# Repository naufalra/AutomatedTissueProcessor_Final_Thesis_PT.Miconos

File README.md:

# 2._NaufalFinalThesis_TissueProcessing_PTMiconos

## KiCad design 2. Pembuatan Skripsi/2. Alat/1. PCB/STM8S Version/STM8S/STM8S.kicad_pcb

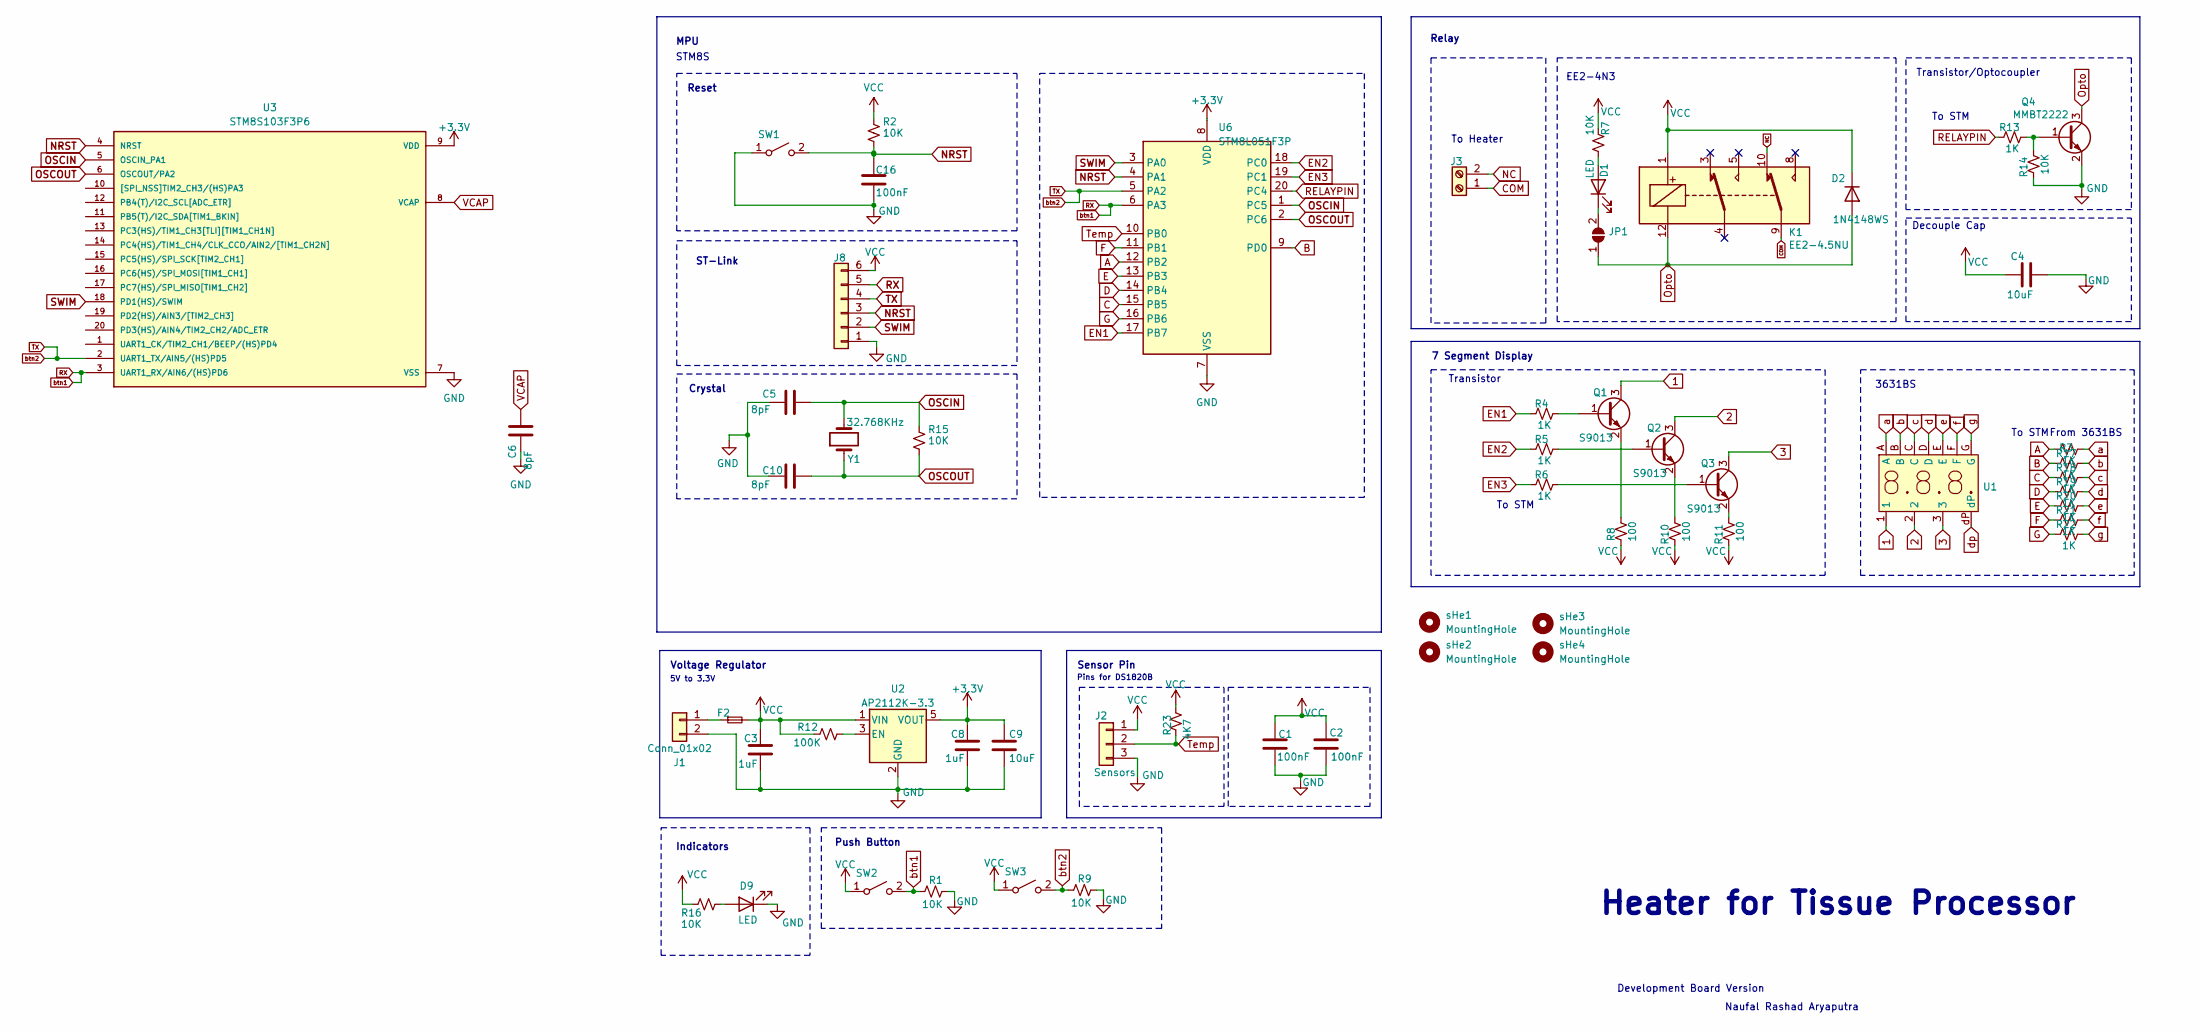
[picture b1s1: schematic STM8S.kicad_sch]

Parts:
C1, C2, C16: 100nF; C_0603_1608Metric_Pad1.08x0.95mm_HandSolder
C3, C8: 1uF; C_0603_1608Metric_Pad1.08x0.95mm_HandSolder
C4, C9: 10uF; C_0603_1608Metric_Pad1.08x0.95mm_HandSolder
C5, C6, C10: 8pF; C_0603_1608Metric_Pad1.08x0.95mm_HandSolder
D1: LED; LED_0603_1608Metric_Pad1.05x0.95mm_HandSolder
D2: 1N4148WS; D_SOD-323
D9: LED; LED_D3.0mm
F2: Fuse_Small; Fuse_1812_4532Metric_Pad1.30x3.40mm_HandSolder
J1: Conn_01x02; JST_XH_B2B-XH-A_1x02_P2.50mm_Vertical
J2: Sensors; JST_XH_B3B-XH-A_1x03_P2.50mm_Vertical
J3: Screw_Terminal_01x02; TerminalBlock_Phoenix_MKDS-1,5-2-5.08_1x02_P5.08mm_Horizont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
J8: Conn_01x06; PinHeader_1x06_P2.54mm_Vertical
JP1: SolderJumper_2_Open; SolderJumper-2_P1.3mm_Open_TrianglePad1.0x1.5mm
K1: EE2-4.5NU; Relay_DPDT_Kemet_EE2_NU
Q1, Q2, Q3: S9013; SOT-23
Q4: MMBT2222; SOT-23
R1, R2, R7, R9, R14, R15, R16: 10K; R_0603_1608Metric_Pad0.98x0.95mm_HandSolder
R3, R4, R5, R6, R13, R17, R18, R19, R20, R21, R22: 1K; R_0603_1608Metric_Pad0.98x0.95mm_HandSolder
R8, R10, R11: 100; R_0603_1608Metric_Pad0.98x0.95mm_HandSolder
R12: 100K; R_0603_1608Metric_Pad0.98x0.95mm_HandSolder
R23: 4K7; R_0603_1608Metric_Pad0.98x0.95mm_HandSolder
SW1: SW_SPST; SW_PUSH_6mm_H5mm
SW2, SW3: SW_SPST; SW_PUSH_6mm_H13mm
U1: 3631BS 7Segment 3Digit
U2: AP2112K-3.3; SOT-23-5
U3: STM8S103F3P6; SOP65P640X120-20N
U6: STM8L051F3P; TSSOP-20_4.4x6.5mm_P0.65mm
Y1: 32.768KHz; Crystal_SMD_SeikoEpson_MC306-4Pin_8.0x3.2mm
sHe1, sHe2, sHe3, sHe4: MountingHole; MountingHole_3mm_Pad_Via

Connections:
1: Q1.3 (C), U1.1
2: Q2.3 (C), U1.2
3: Q3.3 (C), U1.3
+3.3V: C8.1, C9.1, U2.5 (VOUT), U3.9 (VDD), U6.8 (VDD)
A: R3.2, U6.12 (PB2)
B: R17.2, U6.9 (PD0)
C: R18.2, U6.15 (PB5)
COM: J3.1, K1.9
D: R19.2, U6.14 (PB4)
E: R20.2, U6.13 (PB3)
EN1: R4.2, U6.17 (PB7)
EN2: R5.2, U6.18 (PC0)
EN3: R6.2, U6.19 (PC1)
F: R21.2, U6.11 (PB1)
G: R22.2, U6.16 (PB6)
GND: C1.2, C2.2, C3.2, C4.2, C5.2, C6.2, C8.2, C9.2, C10.2, C16.2, D9.1 (K), J1.2, J2.3, J8.1, Q4.2 (E), R1.1, R9.1, R14.2, SW1.1 (A), U2.2 (GND), U3.7 (VSS), U6.7 (VSS)
NC: J3.2, K1.10
NRST: C16.1, J8.3, R2.1, SW1.2 (B), U3.4 (NRST), U6.4 (PA1)
unnamed: D1.2 (A), R7.2
unnamed: D1.1 (K), JP1.2 (B)
unnamed: D9.2 (A), R16.2
unnamed: F2.1, J1.1
unnamed: Q1.1 (B), R4.1
unnamed: Q1.2 (E), R8.1
unnamed: Q2.1 (B), R5.1
unnamed: Q2.2 (E), R10.1
unnamed: Q3.1 (B), R6.1
unnamed: Q3.2 (E), R11.1
unnamed: Q4.1 (B), R13.1, R14.1
unnamed: R12.2, U2.3 (EN)
OSCIN: C5.1, R15.2, U3.5 (OSCIN_PA1), U6.1 (PC5), Y1.2
OSCOUT: C10.1, R15.1, U3.6 (OSCOUT/PA2), U6.2 (PC6), Y1.1
Opto: D2.2 (A), JP1.1 (A), K1.12, Q4.3 (C)
RELAYPIN: R13.2, U6.20 (PC4)
RX: J8.5, R1.2, SW2.2 (B), U3.3 (UART1_RX/AIN6/(HS)PD6), U6.6 (PA3)
SWIM: J8.2, U3.18 (PD1(HS)/SWIM), U6.3 (PA0)
TX: J8.4, R9.2, SW3.2 (B), U3.2 (UART1_TX/AIN5/(HS)PD5), U6.5 (PA2)
Temp: J2.2, R23.1, U6.10 (PB0)
VCAP: C6.1, U3.8 (VCAP)
VCC: C1.1, C2.1, C3.1, C4.1, D2.1 (K), F2.2, J2.1, J8.6, K1.1, R2.2, R7.1, R8.2, R10.2, R11.2, R12.1, R16.1, R23.2, SW2.1 (A), SW3.1 (A), U2.1 (VIN)
a: R3.1, U1.A
b: R17.1, U1.B
c: R18.1, U1.C
d: R19.1, U1.D
dp: U1.dP
e: R20.1, U1.E
f: R21.1, U1.F
g: R22.1, U1.G

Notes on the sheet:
5V to 3.3V
Reset
To STM
Indicators
To Heater
Crystal
Sensor Pin
Development Board Version
7 Segment Display
ST-Link
Naufal Rashad Aryaputra
EE2-4N3
Push Button
Heater for Tissue Processor
Decouple Cap
Relay
Voltage Regulator
Transistor
STM8S
MPU
From 3631BS
Transistor/Optocoupler
3631BS
Pins for DS1820B

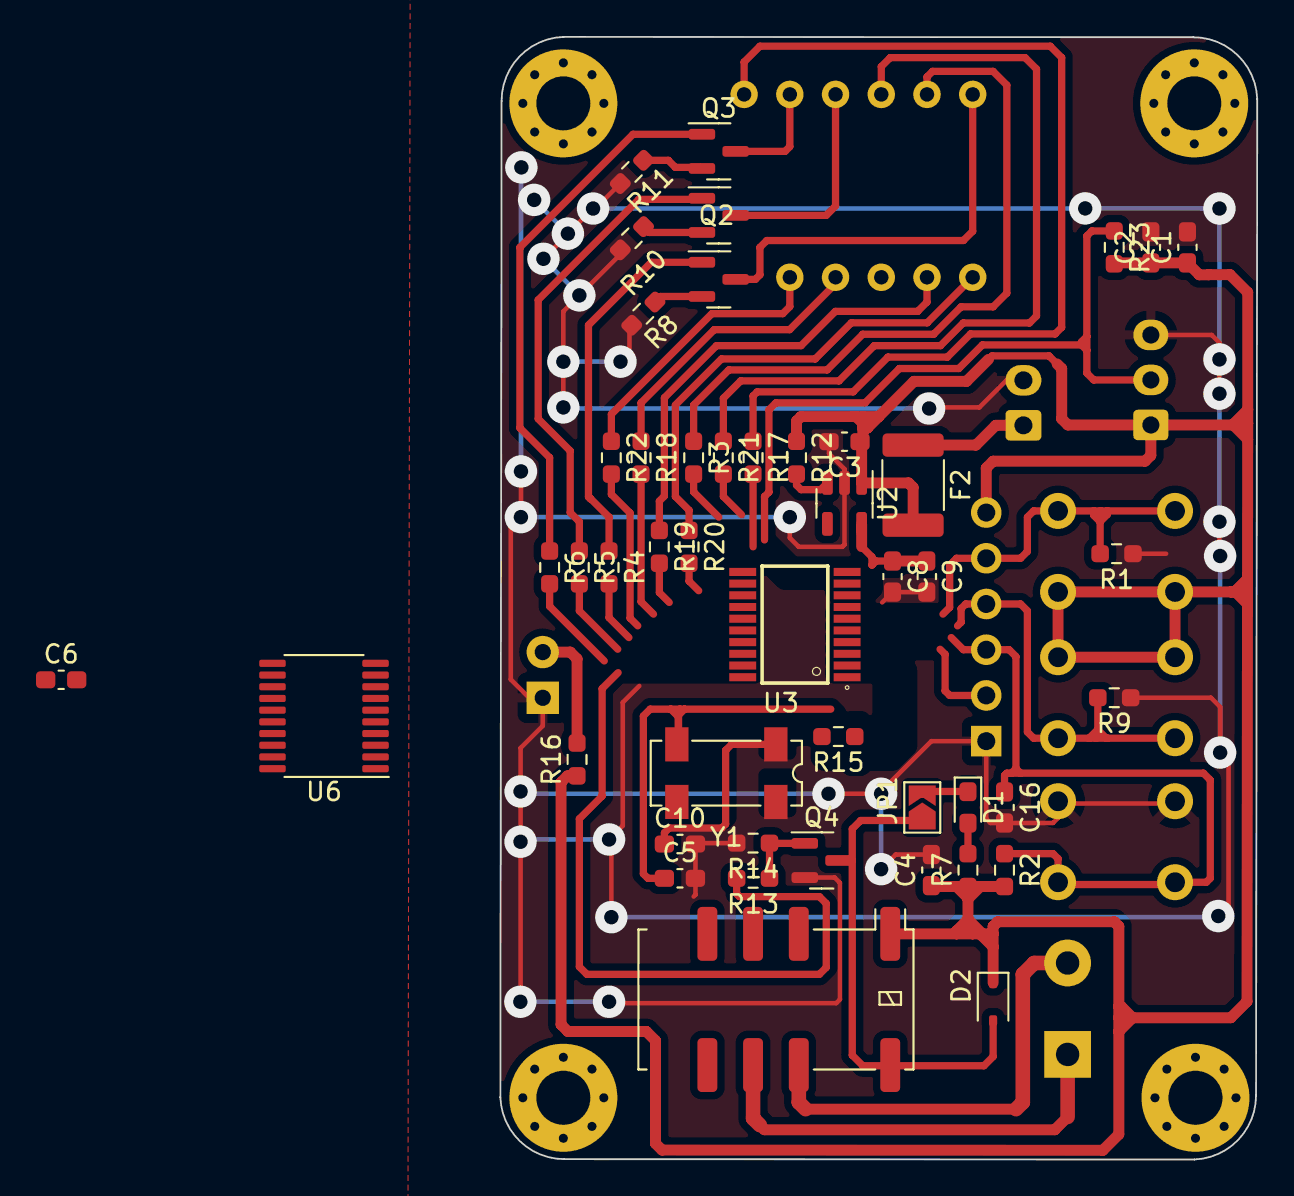
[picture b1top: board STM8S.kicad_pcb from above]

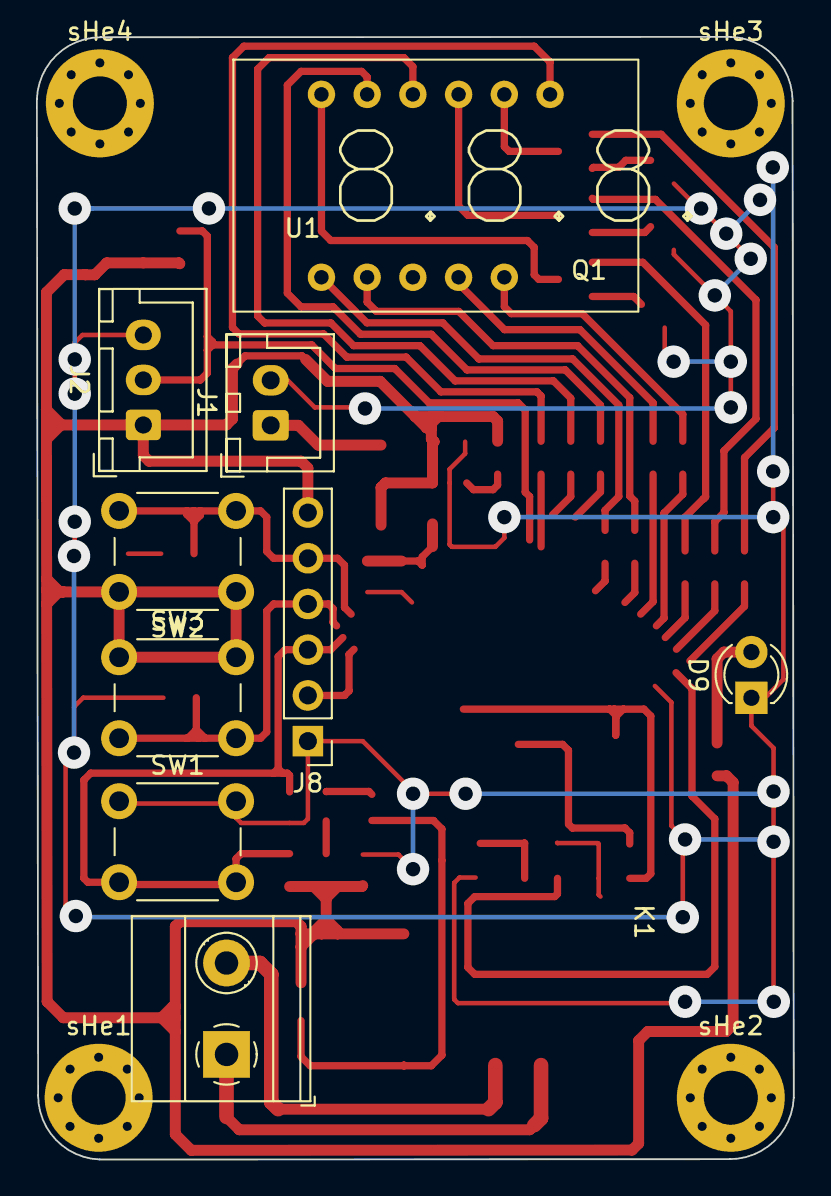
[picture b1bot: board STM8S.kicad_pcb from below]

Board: 2 copper layers, 42.0 x 62.4 mm, 59 parts (13 on the bottom side), 47 nets.

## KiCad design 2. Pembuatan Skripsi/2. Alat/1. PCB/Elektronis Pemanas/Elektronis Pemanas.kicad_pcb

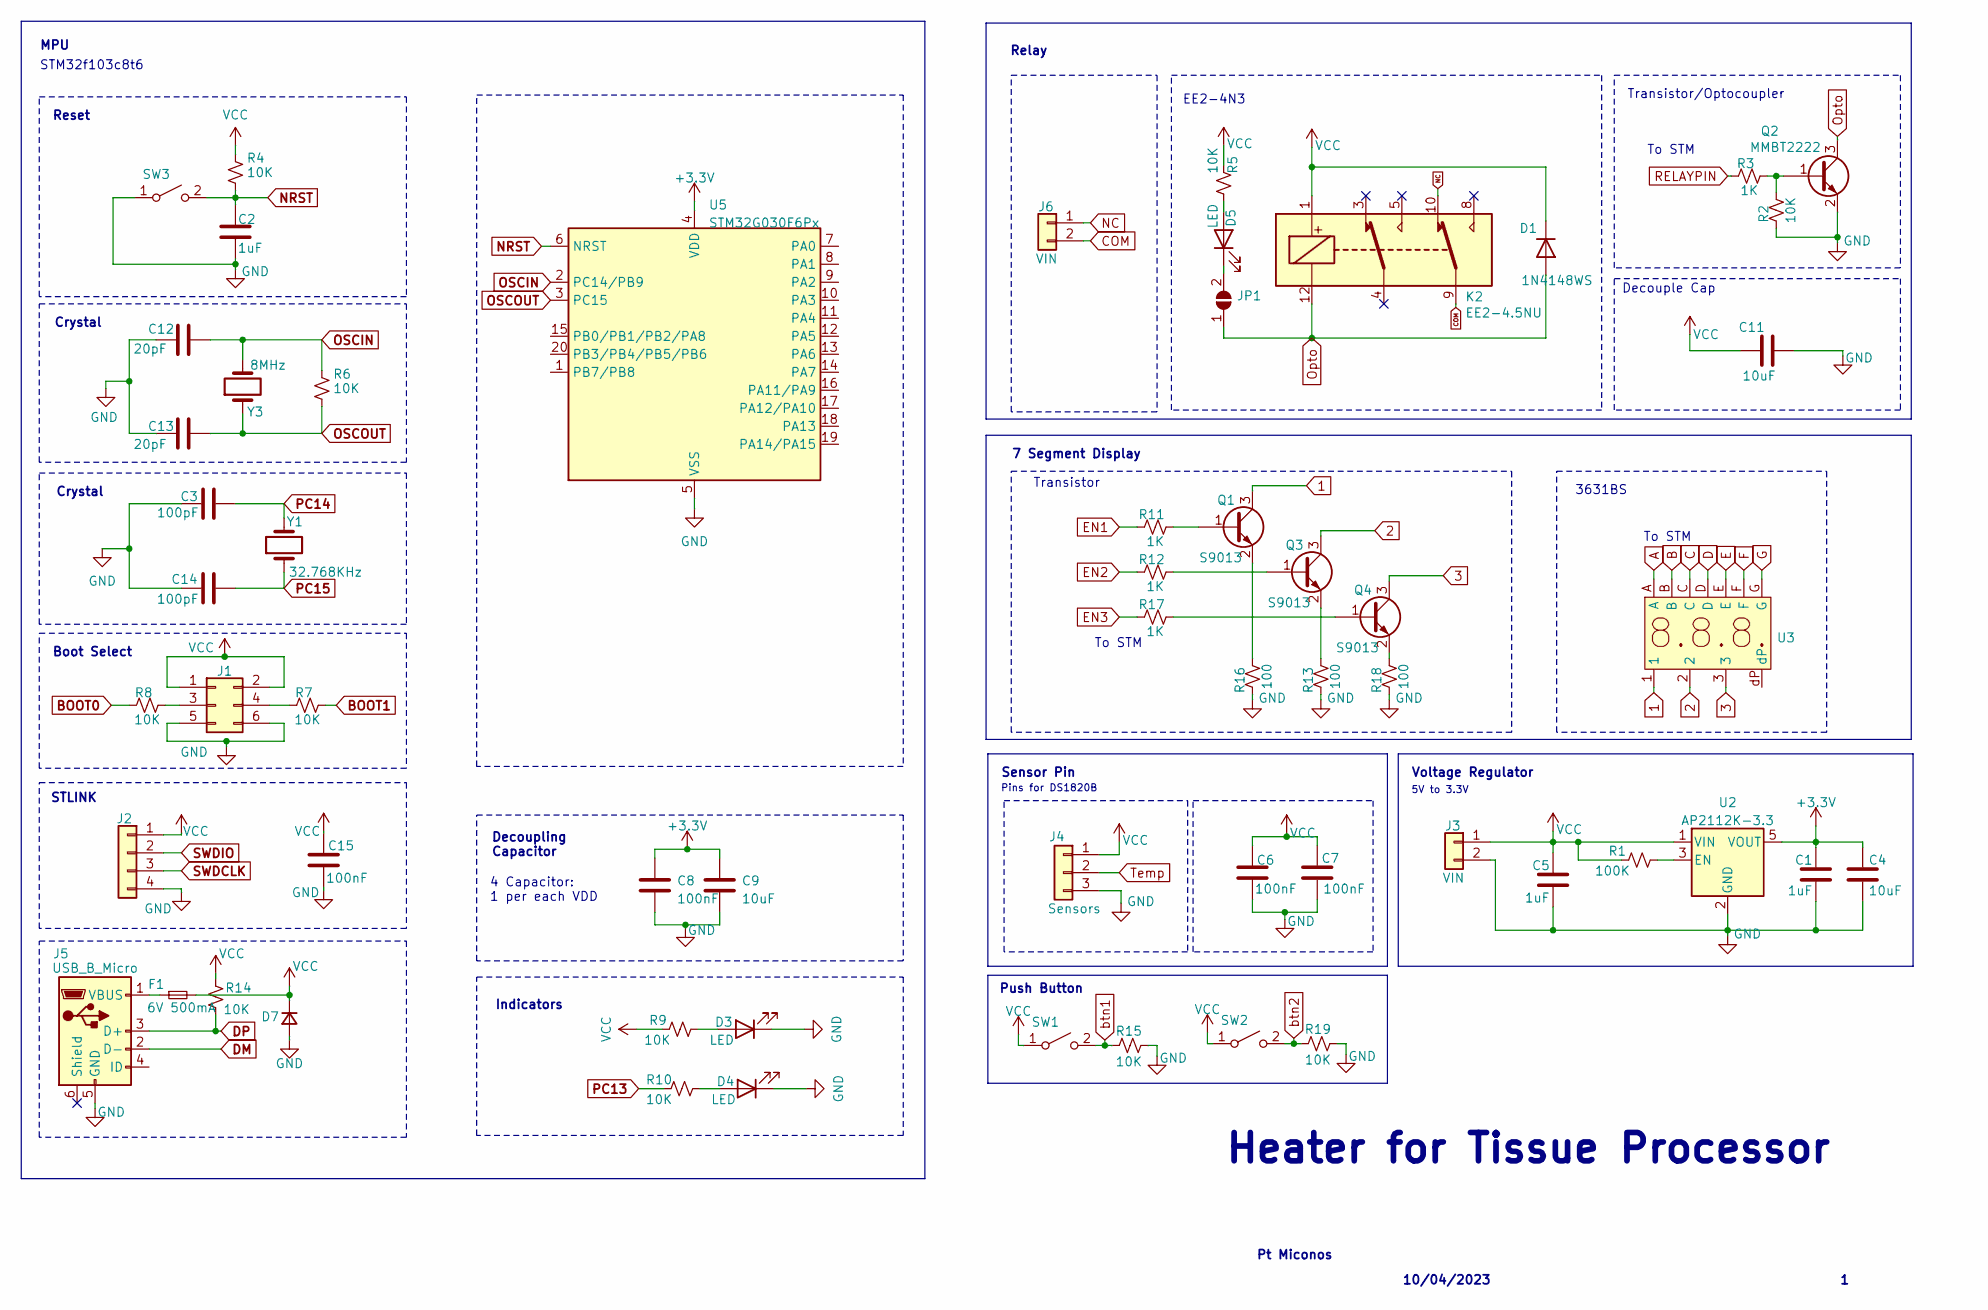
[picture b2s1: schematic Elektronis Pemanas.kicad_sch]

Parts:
C1, C2, C5: 1uF; C_0603_1608Metric_Pad1.08x0.95mm_HandSolder
C3, C14: 100pF; C_0603_1608Metric_Pad1.08x0.95mm_HandSolder
C4, C9, C11: 10uF; C_0603_1608Metric_Pad1.08x0.95mm_HandSolder
C6, C7, C8, C15: 100nF; C_0603_1608Metric_Pad1.08x0.95mm_HandSolder
C12, C13: 20pF; C_0603_1608Metric_Pad1.08x0.95mm_HandSolder
D1: 1N4148WS; D_SOD-323
D3: LED; LED_D3.0mm
D4, D5: LED; LED_0805_2012Metric_Pad1.15x1.40mm_HandSolder
D7: D_Small; D_SMA-SMB_Universal_Handsoldering
F1: 6V 500mA; Fuse_1812_4532Metric_Pad1.30x3.40mm_HandSolder
J1: Conn_02x03_Odd_Even; IDC-Header_2x03_P2.54mm_Vertical
J2: Conn_01x04; JST_XH_B4B-XH-A_1x04_P2.50mm_Vertical
J3, J6: VIN; Banana_Jack_2Pin
J4: Sensors; JST_XH_B3B-XH-A_1x03_P2.50mm_Vertical
J5: USB_B_Micro; USB_Mini-B_Lumberg_2486_01_Horizontal
JP1: SolderJumper_2_Open; SolderJumper-2_P1.3mm_Open_TrianglePad1.0x1.5mm
K2: EE2-4.5NU; Relay_DPDT_Kemet_EE2_NU
Q1, Q3, Q4: S9013; SOT-23
Q2: MMBT2222; SOT-23
R1: 100K; R_0603_1608Metric_Pad0.98x0.95mm_HandSolder
R2, R4, R5, R6, R7, R8, R9, R10, R14, R15, R19: 10K; R_0603_1608Metric_Pad0.98x0.95mm_HandSolder
R3, R11, R12, R17: 1K; R_0603_1608Metric_Pad0.98x0.95mm_HandSolder
R13, R16, R18: 100; R_0603_1608Metric_Pad0.98x0.95mm_HandSolder
SW1, SW2: SW_SPST; SW_PUSH_6mm_H13mm
SW3: SW_SPST; SW_PUSH_6mm_H5mm
U2: AP2112K-3.3; SOT-23-5
U3: 3631BS 7Segment 3Digit
U5: STM32G030F6Px; TSSOP-20_4.4x6.5mm_P0.65mm
Y1: 32.768KHz; Crystal_SMD_SeikoEpson_MC306-4Pin_8.0x3.2mm_HandSoldering
Y3: 8MHz; Crystal_SMD_HC49-SD

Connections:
1: Q1.3 (C), U3.1
2: Q3.3 (C), U3.2
3: Q4.3 (C), U3.3
+3.3V: C1.1, C4.1, C8.1, C9.1, U2.5 (VOUT), U5.4 (VDD)
A: U3.A
B: U3.B
BOOT0: R8.2
BOOT1: R7.1
C: U3.C
COM: J6.2, K2.9
D: U3.D
DM: J5.2 (D-)
DP: J5.3 (D+), R14.1
E: U3.E
EN1: R11.2
EN2: R12.2
EN3: R17.2
F: U3.F
G: U3.G
GND: C1.2, C2.2, C3.2, C4.2, C5.2, C6.2, C7.2, C8.2, C9.2, C11.2, C12.2, C13.2, C14.2, C15.2, D3.1 (K), D4.1 (K), D7.2 (A), J1.5, J1.6, J2.4, J3.2, J4.3, J5.5 (GND), Q2.2 (E), R2.2, R13.2, R15.1, R16.2, R18.2, R19.1, SW3.1 (A), U2.2 (GND), U5.5 (VSS)
NC: J6.1, K2.10
NRST: C2.1, R4.1, SW3.2 (B), U5.6 (NRST)
unnamed: D3.2 (A), R9.2
unnamed: D4.2 (A), R10.2
unnamed: D5.2 (A), R5.2
unnamed: D5.1 (K), JP1.2 (B)
unnamed: J1.3, R8.1
unnamed: J1.4, R7.2
unnamed: F1.1, J5.1 (VBUS)
unnamed: Q1.1 (B), R11.1
unnamed: Q1.2 (E), R16.1
unnamed: Q2.1 (B), R2.1, R3.1
unnamed: Q3.1 (B), R12.1
unnamed: Q3.2 (E), R13.1
unnamed: Q4.1 (B), R17.1
unnamed: Q4.2 (E), R18.1
unnamed: R1.2, U2.3 (EN)
OSCIN: C12.1, R6.2, U5.2 (PC14/PB9), Y3.2
OSCOUT: C13.1, R6.1, U5.3 (PC15), Y3.1
Opto: D1.2 (A), JP1.1 (A), K2.12, Q2.3 (C)
PC13: R10.1
PC14: C3.1, Y1.2
PC15: C14.1, Y1.1
RELAYPIN: R3.2
SWDCLK: J2.3
SWDIO: J2.2
Temp: J4.2
VCC: C5.1, C6.1, C7.1, C11.1, C15.1, D1.1 (K), D7.1 (K), F1.2, J1.1, J1.2, J2.1, J3.1, J4.1, K2.1, R1.1, R4.2, R5.1, R9.1, R14.2, SW1.1 (A), SW2.1 (A), U2.1 (VIN)
btn1: R15.2, SW1.2 (B)
btn2: R19.2, SW2.2 (B)

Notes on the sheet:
5V to 3.3V
EE2-4N3
Transistor
Crystal
To STM
Decouple Cap
7 Segment Display
Heater for Tissue Processor
Relay
Sensor Pin
Boot Select
STLINK
Voltage Regulator
Transistor/Optocoupler
3631BS
Reset
10/04/2023
Push Button
MPU
STM32f103c8t6
Pins for DS1820B
4 Capacitor: 1 per each VDD
Pt Miconos
Indicators
Decoupling Capacitor

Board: 2 copper layers, 59 parts (0 on the bottom side), 32 nets, no tracks yet.

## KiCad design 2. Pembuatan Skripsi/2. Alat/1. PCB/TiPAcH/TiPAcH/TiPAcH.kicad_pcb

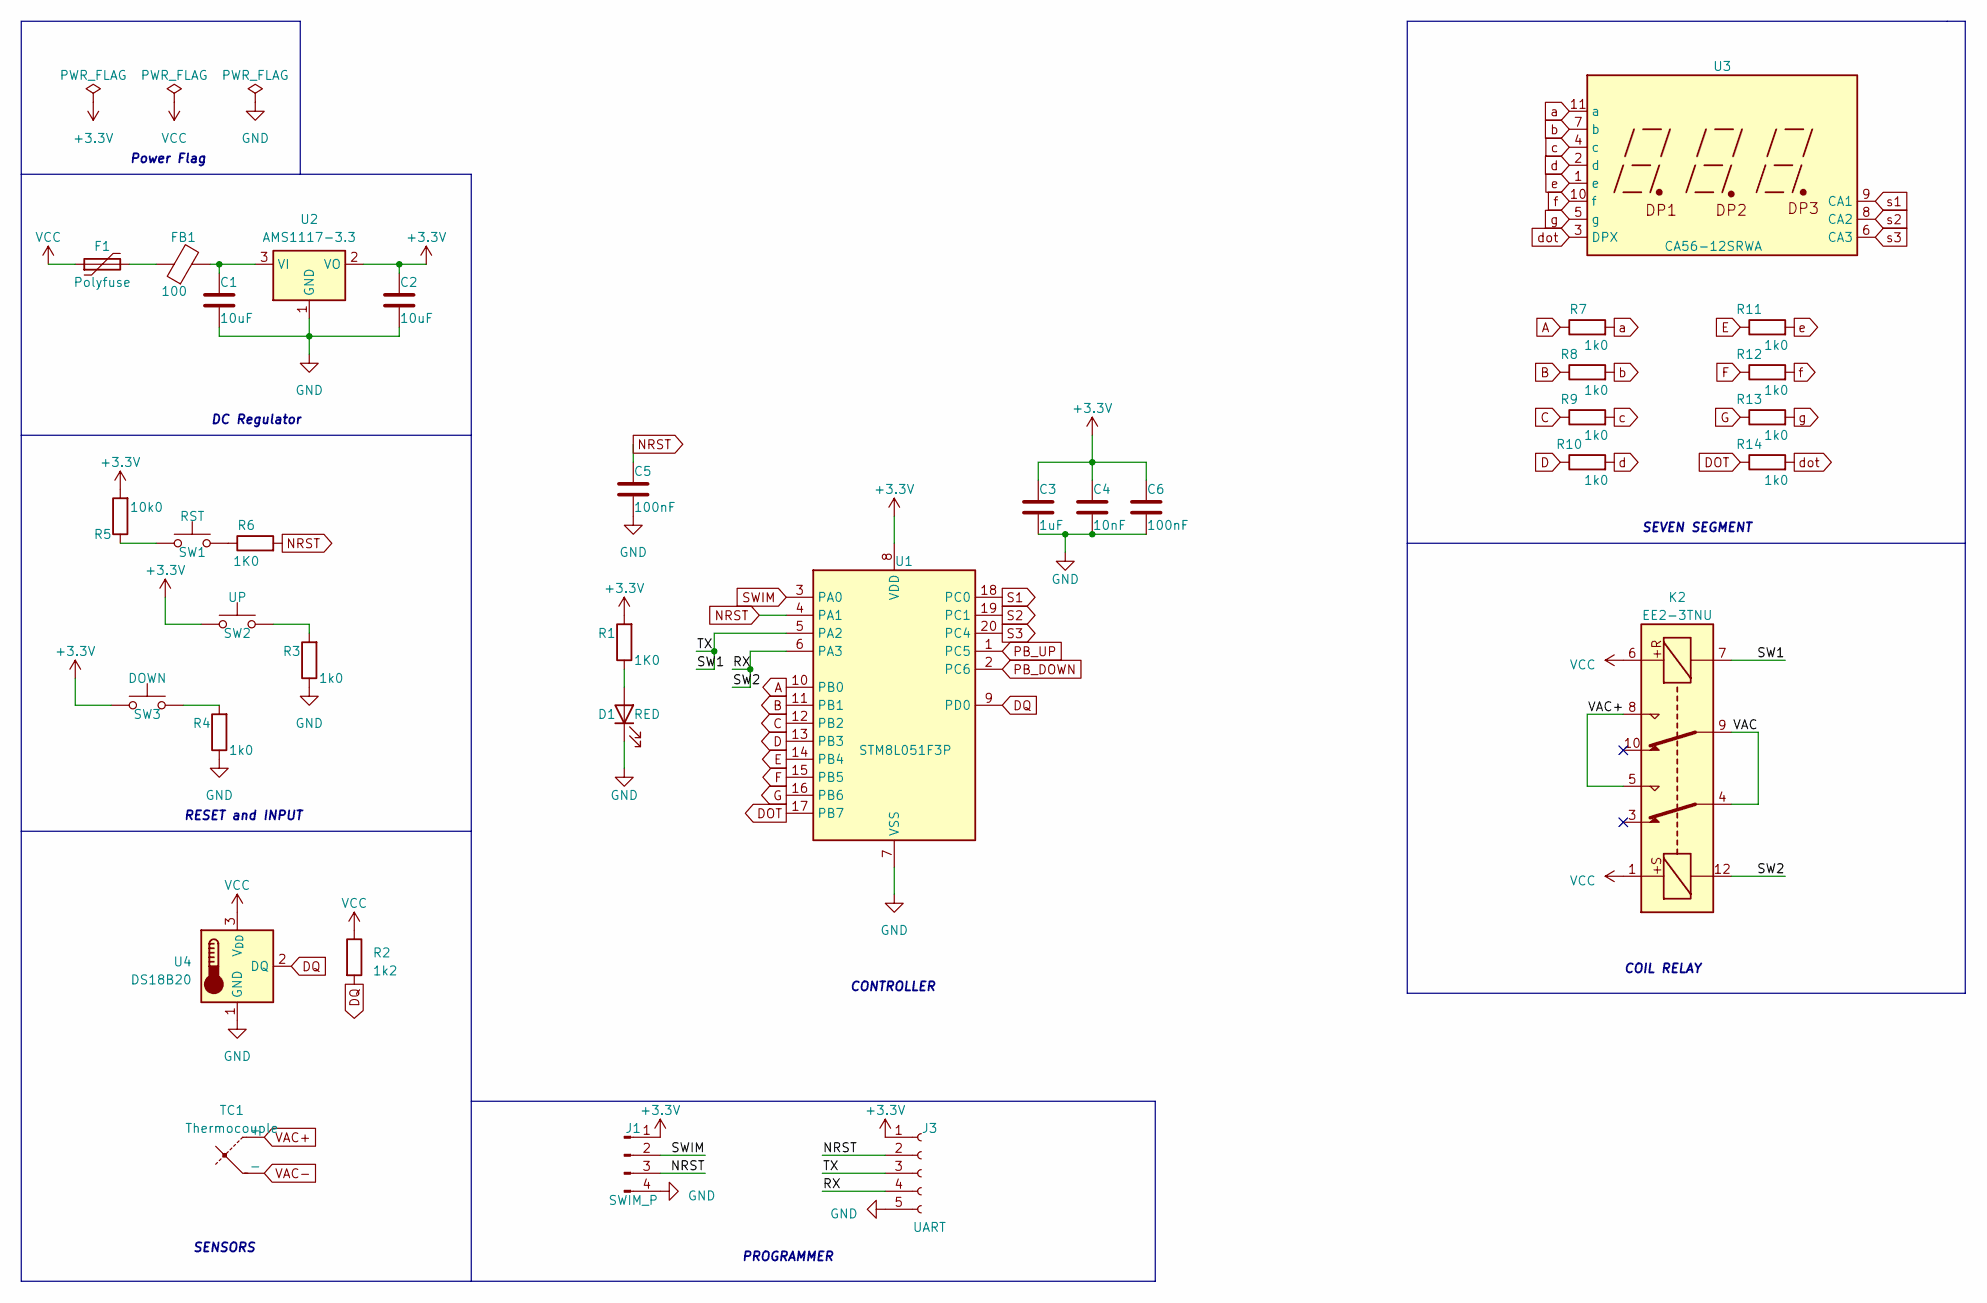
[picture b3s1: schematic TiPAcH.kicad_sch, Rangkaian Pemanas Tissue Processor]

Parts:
C1, C2: 10uF; C_1206_3216Metric
C3: 1uF; C_1206_3216Metric
C4: 10nF; C_1206_3216Metric
C5, C6: 100nF; C_1206_3216Metric
D1: RED; LED_1206_3216Metric
F1: Polyfuse; Fuse_2512_6332Metric
FB1: 100; R_1206_3216Metric
J1: SWIM_P; PinSocket_1x04_P2.54mm_Horizontal
J3: UART; PinSocket_1x05_P2.54mm_Horizontal
K2: EE2-3TNU; Relay_DPDT_Kemet_EE2_NU_DoubleCoil
R1, R6: 1K0; R_1206_3216Metric
R2: 1k2; R_1206_3216Metric
R3, R4, R7, R8, R9, R10, R11, R12, R13, R14: 1k0; R_1206_3216Metric
R5: 10k0; R_1206_3216Metric
SW1: RST; SW_SPST_Omron_B3FS-100xP
SW2: UP; SW_SPST_Omron_B3FS-100xP
SW3: DOWN; SW_SPST_Omron_B3FS-100xP
TC1: Thermocouple; PinSocket_1x02_P2.54mm_Horizontal
U1: STM8L051F3P; TSSOP-20_4.4x6.5mm_P0.65mm
U2: AMS1117-3.3; SOT-223-3_TabPin2
U3: CA56-12SRWA
U4: DS18B20; TO-92_Inline

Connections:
+3.3V: C2.1, C3.1, C4.1, C6.1, J1.1, J3.1, R1.2, R5.2, SW2.1, SW3.1, U1.8 (VDD), U2.2 (VO)
/RX: J3.4, K2.12, U1.6 (PA3)
/SW1: J3.3, K2.7, U1.5 (PA2)
/VAC: K2.4, K2.9
A: R7.1, U1.10 (PB0)
B: R8.1, U1.11 (PB1)
C: R9.1, U1.12 (PB2)
D: R10.1, U1.13 (PB3)
DOT: R14.1, U1.17 (PB7)
DQ: R2.2, U1.9 (PD0), U4.2 (DQ)
E: R11.1, U1.14 (PB4)
F: R12.1, U1.15 (PB5)
G: R13.1, U1.16 (PB6)
GND: C1.2, C2.2, C3.2, C4.2, C5.2, C6.2, D1.1 (K), J1.4, J3.5, R3.1, R4.1, U1.7 (VSS), U2.1 (GND), U4.1 (GND)
NRST: C5.1, J1.3, J3.2, R6.2, U1.4 (PA1)
unnamed: D1.2 (A), R1.1
unnamed: F1.2, FB1.1
unnamed: R3.2, SW2.2
unnamed: R4.2, SW3.2
unnamed: R5.1, SW1.1
unnamed: R6.1, SW1.2
unnamed: C1.1, FB1.2, U2.3 (VI)
PB_DOWN: U1.2 (PC6)
PB_UP: U1.1 (PC5)
S1: U1.18 (PC0)
S2: U1.19 (PC1)
S3: U1.20 (PC4)
SWIM: J1.2, U1.3 (PA0)
VAC+: K2.5, K2.8, TC1.1 (+)
VAC-: TC1.2 (-)
VCC: F1.1, K2.1, K2.6, R2.1, U4.3 (V_{DD})
a: R7.2, U3.11 (a)
b: R8.2, U3.7 (b)
c: R9.2, U3.4 (c)
d: R10.2, U3.2 (d)
dot: R14.2, U3.3 (DPX)
e: R11.2, U3.1 (e)
f: R12.2, U3.10 (f)
g: R13.2, U3.5 (g)
s1: U3.9 (CA1)
s2: U3.8 (CA2)
s3: U3.6 (CA3)

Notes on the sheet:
DC Regulator
SENSORS
PROGRAMMER
COIL RELAY
CONTROLLER
SEVEN SEGMENT
RESET and INPUT
Power Flag

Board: 2 copper layers, 34 parts (0 on the bottom side), 33 nets, no tracks yet.

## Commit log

2023-03-24 Final Update of Kerja Praktek
    Datasheet is added
2023-04-04 *Major Changes
    - Arif Reference added
    - STM8 + STM32F reference are fully added
    - STM32G are currently under development
2023-04-13 *Merapihkan
    *All of the Documents are moved to Laporan
    *Numpang folder added
2023-04-15 *New Custom Libs added
    - 3631BS Seven segment are added
2023-05-11 First Revision of PCB Design
    - Waiting for Approval
2023-05-29 *Major Update*
    - STM8S PCB jumpers are relocated to make it easier to solder it
    - ATMEGA328 version is added and revised for backup option
    - Arduino Code for ATMEGA328 is added.
2023-06-07 Huge Update
    - New program
    - Report updated
2023-06-07 Programming feature added
    - Serial send to ESP (as a slave)
2023-06-12 Huge update for ATMEGA328P Board
    Program is fully working:
    - Get parameter, sensor data, led status, relay status.
    - Show parameter on SevSeg
    - Connected to NodeRed
    - Board design is revised based on actual board
2023-06-28 Minor changes
